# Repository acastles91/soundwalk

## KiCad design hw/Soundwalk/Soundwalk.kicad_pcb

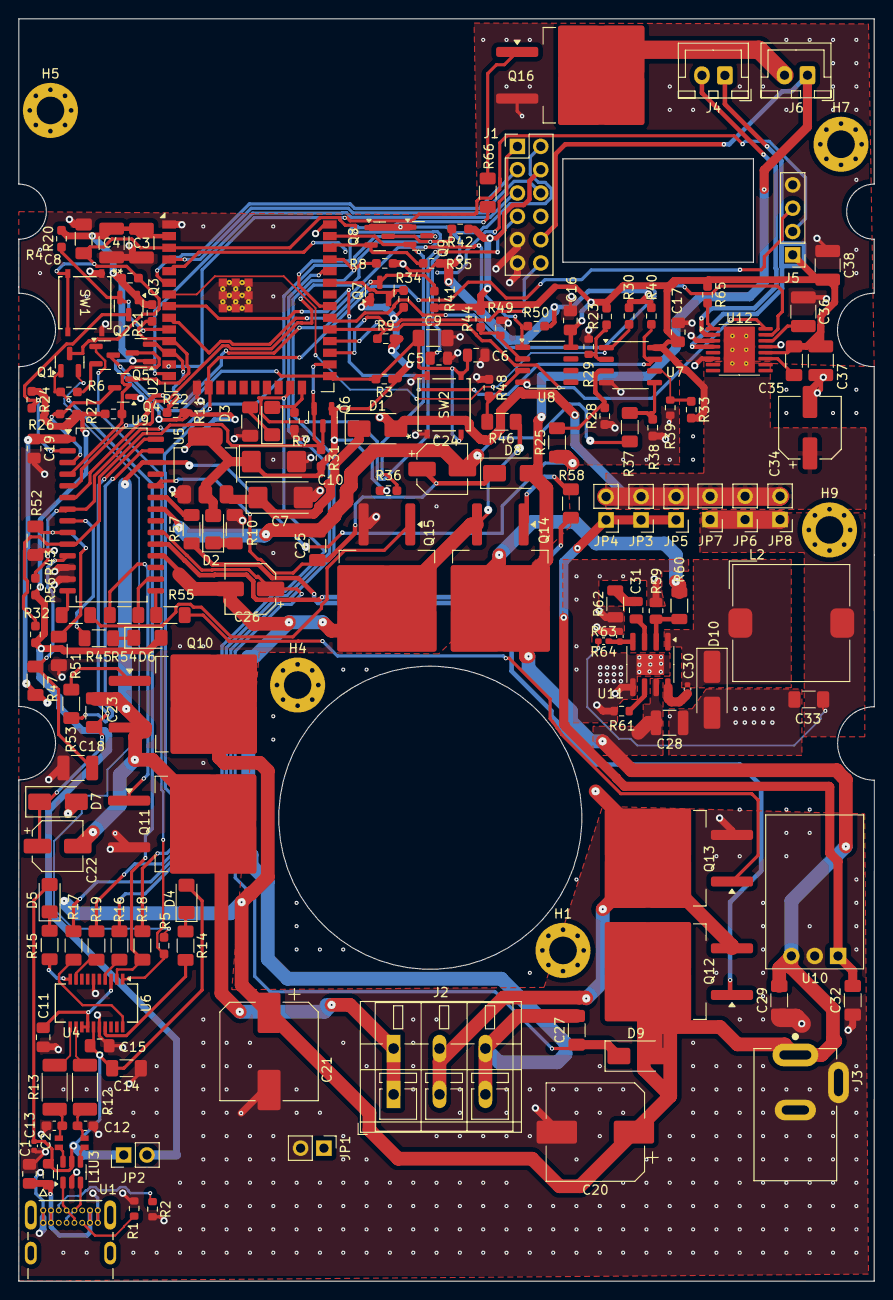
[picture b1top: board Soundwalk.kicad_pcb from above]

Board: 4 copper layers, 93.1 x 137.5 mm, 165 parts (0 on the bottom side), 109 nets.

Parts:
C1, C11, C15, C16, C17, C19: 0.1uF X7R 50V 0805; C_0805_2012Metric_Pad1.18x1.45mm_HandSolder
C2: 100n; C_0402_1005Metric
C3, C36, C37, C38: 10uF; C_1210_3225Metric_Pad1.33x2.70mm_HandSolder
C4: 22uF; C_1210_3225Metric_Pad1.33x2.70mm_HandSolder
C5, C6: 1uF; C_0805_2012Metric
C7, C10: 10uF 25V 2312 Tantalum; CP_EIA-6032-15_Kemet-U
C8, C9, C35: 0.1uF; C_1206_3216Metric_Pad1.33x1.80mm_HandSolder
C12, C13: 47pF; C_0603_1608Metric_Pad1.08x0.95mm_HandSolder
C14: 4.7uF 16V 1206 Tantalum; C_1206_3216Metric_Pad1.33x1.80mm_HandSolder
C18: 10uF 50V X7R; C_1210_3225Metric_Pad1.33x2.70mm_HandSolder
C20, C21: 330uF 35V; CP_Elec_10x10.5
C22, C24, C26: 10uF; CP_Elec_5x5.7
C23, C25, C27: 10uF 50V X7R; C_1206_3216Metric_Pad1.33x1.80mm_HandSolder
C28: 10uF 50V X7R 1210; C_1210_3225Metric
C29, C32, C33: 22uF 6.3V; C_1206_3216Metric_Pad1.33x1.80mm_HandSolder
C30: 100nF; C_0402_1005Metric
C31: 150pF 0805; C_0805_2012Metric
C34: C_Polarized; CP_Elec_6.3x5.9
D1: SS14; D_SMA
D2, D4, D5: LED - Yellow; LED_1206_3216Metric_Pad1.42x1.75mm_HandSolder
D3, D6: LED - Red; LED_1206_3216Metric_Pad1.42x1.75mm_HandSolder
D7, D8, D9: US1J; D_SMA
D10: D_Schottky; D_SMA_Handsoldering
H1, H4, H5, H7, H9: MountingHole_Pad; MountingHole_3mm_Pad_Via
J1: Conn_02x06_Odd_Even; PinHeader_2x06_P2.54mm_Vertical
J2: Screw_Terminal_01x03; TerminalBlock_WAGO_236-403_1x03_P5.00mm_45Degree
J3: PJ-002B; CUI_PJ-002B
J4, J6: Screw_Terminal_01x02; JST_XH_B2B-XH-A_1x02_P2.50mm_Vertical
J5: Conn_01x04_Socket; PinHeader_1x04_P2.54mm_Vertical
JP1, JP2, JP3, JP4, JP5, JP6, JP7, JP8: Jumper_2_Open; PinHeader_1x02_P2.54mm_Vertical
L1: L_Ferrite; L_0805_2012Metric_Pad1.05x1.20mm_HandSolder
L2: 15uH; L_TDK_SLF12565
Q1, Q2: S8050; SOT-23
Q3, Q4, Q5, Q6, Q7, Q8, Q9: 2N7002E; SOT-23
Q10, Q11, Q12, Q13, Q14, Q15, Q16: IRLZ44N; TO-263-2
R1, R2, R29, R39, R49: 5.1k; R_0603_1608Metric
R3, R4, R5, R6, R7, R8, R9, R20, R21, R22, R23, R24, R26, R27, R28, R30, R31, R32, R33, R34, R35, R36, R38, R40, R41, R42, R43, R44, R48, R50, R65: 10K; R_0603_1608Metric_Pad0.98x0.95mm_HandSolder
R10, R11: 220R; R_1206_3216Metric_Pad1.30x1.75mm_HandSolder
R12, R13: 27R; R_2010_5025Metric_Pad1.40x2.65mm_HandSolder
R14, R15, R16, R17, R45, R51, R53, R57, R58, R66: 1K; R_1206_3216Metric_Pad1.30x1.75mm_HandSolder
R18, R19: 0R; R_1206_3216Metric_Pad1.30x1.75mm_HandSolder
R25, R37, R46: 33K; R_1206_3216Metric_Pad1.30x1.75mm_HandSolder
R47: 100K; R_1206_3216Metric_Pad1.30x1.75mm_HandSolder
R52: 1M; R_1206_3216Metric_Pad1.30x1.75mm_HandSolder
R54, R55, R56: 100R; R_1206_3216Metric_Pad1.30x1.75mm_HandSolder
R59: 17.4K 0805; R_0805_2012Metric
R60, R62: 100K 1206; R_1206_3216Metric
R61: 200K 0603; R_0603_1608Metric
R63: 40.2k; C_0402_1005Metric_Pad0.74x0.62mm_HandSolder
R64: 210k; C_0402_1005Metric_Pad0.74x0.62mm_HandSolder
SW1, SW2: PTS526 SM15 SMTR2 LFS; SON4_PTS526 SM15 SMTR2 LFS_CNK
U1: 2137160001-Molex-USB-C-Connector; MOLEX_2137160001
U2: ESP32-WROOM-E; ESP32-WROOM-32E
U3: USBLC6-2SC6; SOT-23-6
U4: SRF3216A-Common_Mode_Choke; Bourns_SRF3216A
U5: NCP1117-3.3_SOT223; SOT-223-3_TabPin2
U6: FT231XS; SSOP-20_3.9x8.7mm_P0.635mm
U7, U8: LM393; SOP-8_3.9x4.9mm_P1.27mm
U9: IR2136; SOIC-28W_7.5x18.7mm_P1.27mm
U10: OKI-78SR-5_1.5-W36H-C; Converter_DCDC_Murata_OKI-78SR_Horizontal
U11: SOIC-8-1EP_3.9x4.9mm_P1.27mm_EP2.29x3mm
U12: DRV8833PWP; HTSSOP-16-1EP_4.4x5mm_P0.65mm_EP3.4x5mm_Mask2.46x2.31mm_The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

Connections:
+3.3V: C3.1, C4.1, C10.1, D2.2 (A), J1.2, Q3.1 (G), Q4.1 (G), Q5.1 (G), Q6.1 (G), Q7.1 (G), Q8.1 (G), Q9.1 (G), R3.1, R4.1, R8.2, R9.2, R20.2, R21.2, R22.2, R30.1, R31.2, R34.2, R35.2, R36.2, R40.1, R50.1, U2.2 (3V3), U5.2 (VO)
+5V: C16.1, C17.1, C34.1, C35.2, C37.2, C38.1, D1.2 (A), D6.2 (A), J1.4, J5.1, JP2.2 (B), JP3.2 (B), JP4.2 (B), JP5.2 (B), JP6.2 (B), JP7.2 (B), JP8.2 (B), R23.2, R24.1, R26.1, R27.1, R32.1, R33.2, R41.1, R42.1, R43.1, R44.2, R65.1, U7.8 (V+), U8.8 (V+), U12.12 (VM)
+12V: C19.1, C20.1, C21.1, C28.2, C29.2, D7.2 (A), D8.2 (A), D9.2 (A), J1.10, J3.1, J6.1, Q10.2 (D), Q12.2 (D), Q14.2 (D), R47.2, R60.2, U9.1 (VCC), U10.1 (IN), U11.7 (VIN)
/3-PH/3PH-ZC1: R30.2, U2.7 (GPIO35/ADC1_CH7), U7.1
/3-PH/3PH-ZC2: R40.2, U2.8 (32K_XP/GPIO32/ADC1_CH4), U7.7
/3-PH/3PH-ZC3: R50.2, U2.9 (32K_XN/GPIO33/ADC1_CH5), U8.1
/3-PH/HIN1: Q3.3 (D), R24.2, U9.2 (HIN1)
/3-PH/HIN2: Q4.3 (D), R26.2, U9.3 (HIN2)
/3-PH/HIN3: Q5.3 (D), R27.2, U9.4 (HIN3)
/3-PH/IR2136-EN: Q6.2 (S), Q6.3 (D), R31.1, R32.2, U2.26 (ADC2_CH0/GPIO4), U9.10 (EN)
/3-PH/IR2136-FAULT: R45.2, U9.8 (FAULT)
/3-PH/IR2136-FAULT-LED: D6.1 (K), R45.1
/3-PH/IR2136-HO1: R53.2, U9.27 (HO1)
/3-PH/IR2136-HO1-R: Q10.1 (G), R53.1
/3-PH/IR2136-HO2: R57.2, U9.23 (HO2)
/3-PH/IR2136-HO2-R: Q12.1 (G), R57.1
/3-PH/IR2136-HO3: R58.2, U9.19 (HO3)
/3-PH/IR2136-HO3-R: Q14.1 (G), R58.1
/3-PH/IR2136-ITRIP: R51.1, R52.2, U9.9 (ITRIP)
/3-PH/IR2136-LIN1: Q7.2 (S), R34.1, U2.33 (GPIO21)
/3-PH/IR2136-LIN2: Q8.2 (S), R35.1, U2.36 (GPIO22)
/3-PH/IR2136-LIN3: Q9.2 (S), R36.1, U2.37 (GPIO23)
/3-PH/IR2136-LO1: R54.2, U9.16 (LO1)
/3-PH/IR2136-LO1-R: Q11.1 (G), R54.1
/3-PH/IR2136-LO2: R55.2, U9.15 (LO2)
/3-PH/IR2136-LO2-R: Q13.1 (G), R55.1
/3-PH/IR2136-LO3: R56.2, U9.14 (LO3)
/3-PH/IR2136-LO3-R: Q15.1 (G), R56.1
/3-PH/IR2136-RCIN: C18.1, R47.1, U9.11 (RCIN)
/3-PH/IR2136-VB1: C22.1, C23.1, D7.1 (K), U9.28 (VB1)
/3-PH/IR2136-VB2: C24.1, C25.1, D8.1 (K), U9.24 (VB2)
/3-PH/IR2136-VB3: C26.1, C27.1, D9.1 (K), U9.20 (VB3)
/3-PH/IR2136_HIN1: Q3.2 (S), R20.1, U2.10 (DAC_1/ADC2_CH8/GPIO25)
/3-PH/IR2136_HIN2: Q4.2 (S), R21.1, U2.11 (DAC_2/ADC2_CH9/GPIO26)
/3-PH/IR2136_HIN3: Q5.2 (S), R22.1, U2.12 (ADC2_CH7/GPIO27)
/3-PH/IR2136_VS1: C22.2, C23.2, J2.1, Q10.3 (S), Q11.2 (D), R25.1, U9.26 (VS1)
/3-PH/IR2136_VS2: C24.2, C25.2, J2.2, Q12.3 (S), Q13.2 (D), R37.1, U9.22 (VS2)
/3-PH/IR2136_VS3: C26.2, C27.2, J2.3, Q14.3 (S), Q15.2 (D), R46.1, U9.18 (VS3)
/3-PH/LIN1: Q7.3 (D), R41.2, U9.5 (LIN1)
/3-PH/LIN2: Q8.3 (D), R42.2, U9.6 (LIN2)
/3-PH/LIN3: Q9.3 (D), R43.2, U9.7 (LIN3)
/3-PH/LM393-COIL1: R25.2, R28.2, U7.3 (+)
/3-PH/LM393-COIL2: R37.2, R38.2, U7.5 (+)
/3-PH/LM393-COIL3: R46.2, R48.2, U8.3 (+)
/3-PH/LM393-VREF1: R23.1, R29.1, U7.2 (-)
/3-PH/LM393-VREF2: R33.1, R39.1, U7.6 (-)
/3-PH/LM393-VREF3: R44.1, R49.1, U8.2 (-)
/ESP32-WROOM-32/ESP32-12VLED: R66.2, U2.31 (GPIO19)
/ESP32-WROOM-32/ESP32-AIN2: U2.30 (GPIO18), U12.15 (AIN2)
/ESP32-WROOM-32/ESP32-AUX-1: J1.8, U2.28 (GPIO17)
/ESP32-WROOM-32/ESP32-AUX-2: J1.12, U2.27 (GPIO16)
/ESP32-WROOM-32/ESP32-AUX-4: J1.5, U2.14 (MTDI/GPIO12/ADC2_CH5)
/ESP32-WROOM-32/ESP32-AUX-5: J1.7, R19.1, U2.23 (MTDO/GPIO15/ADC2_CH3)
/ESP32-WROOM-32/ESP32-AUX-6: J1.3, U2.6 (GPIO34/ADC1_CH6)
/ESP32-WROOM-32/ESP32-ENABLE: C5.1, C8.1, Q1.3 (C), R4.2, SW1.3, SW1.4, U2.3 (EN/CHIP_PU)
/ESP32-WROOM-32/ESP32-GPIO0: C6.1, C9.1, Q2.3 (C), R3.2, SW2.3, SW2.4, U2.25 (GPIO0/BOOT/ADC2_CH1)
/ESP32-WROOM-32/ESP32-GPIO2: D3.2 (A), R7.2, U2.24 (ADC2_CH2/GPIO2)
/ESP32-WROOM-32/ESP32-GPIO5: R9.1, U2.29 (GPIO5), U12.16 (AIN1)
/ESP32-WROOM-32/ESP32-GPIO13: J5.3, R18.1, U2.16 (MTCK/GPIO13/ADC2_CH4)
/ESP32-WROOM-32/ESP32-LED-CLK: J5.2, U2.13 (MTMS/GPIO14/ADC2_CH6)
/ESP32-WROOM-32/ESP32-RXD0: R17.1, U2.34 (U0RXD/GPIO3)
/ESP32-WROOM-32/ESP32-SENSOR-VN: J1.1, U2.5 (SENSOR_VN/GPIO39/ADC1_CH3)
/ESP32-WROOM-32/ESP32-SENSOR-VP: J1.6, U2.4 (SENSOR_VP/GPIO36/ADC1_CH0)
/ESP32-WROOM-32/ESP32-TXD0: R8.1, R16.1, U2.35 (U0TXD/GPIO1)
/ESP32-WROOM-32/FT231XS-CTS: R19.2, U6.9 (~CTS)
/ESP32-WROOM-32/FT231XS-DTR: Q2.1 (E), R5.1, U6.1 (~DTR)
/ESP32-WROOM-32/FT231XS-RTS: Q1.1 (E), R6.1, R18.2, U6.2 (~RTS)
/ESP32-WROOM-32/FT231XS-RXD: R16.2, U6.4 (RXD)
/ESP32-WROOM-32/FT231XS-TXD: R17.2, U6.20 (TXD)
/ESP32-WROOM-32/USBDM: R12.2, U6.12 (USBDM)
/ESP32-WROOM-32/USBDP: R13.2, U6.11 (USBDP)
/ESP32-WROOM-32/USB_CMC_D+: U3.6 (I/O1), U4.3
/ESP32-WROOM-32/USB_CMC_D-: U3.4 (I/O2), U4.4
/ESP32-WROOM-32/USB_CONN_CC1: R2.1, U1.A5 (CC1)
/ESP32-WROOM-32/USB_CONN_CC2: R1.1, U1.B5 (CC2)
/ESP32-WROOM-32/USB_CONN_D+: U1.A6 (DP1), U1.B6 (DP2), U3.1 (I/O1)
/ESP32-WROOM-32/USB_CONN_D-: U1.A7 (DN1), U1.B7 (DN2), U3.3 (I/O2)
/ESP32-WROOM-32/USB_FT231XS_D+: C13.1, R13.1, U4.2
/ESP32-WROOM-32/USB_FT231XS_D-: C12.1, R12.1, U4.1
/Power/EN: R59.2, R60.1, U11.2 (EN)
GND: C1.2, C2.1, C3.2, C4.2, C5.2, C6.2, C7.2, C8.2, C9.2, C10.2, C11.2, C12.2, C13.2, C14.2, C15.2, C16.2, C17.2, C18.2, C19.2, C20.2, C21.2, C28.1, C29.1, C32.1, C33.1, C34.2, C36.1, C37.1, C38.2, D10.2 (A), J1.9, J1.11, J3.2, J3.3, J5.4, JP1.2 (B), Q11.3 (S), Q13.3 (S), Q15.3 (S), Q16.3 (S), R1.2, R2.2, R7.1, R10.1, R11.1, R28.1, R29.2, R38.1, R39.2, R48.1, R49.2, R51.2, R52.1, R59.1, R61.1, R62.1, R63.1, SW1.1, SW1.2, SW2.1, SW2.2, U1.A1 (GND), U1.A12 (GND), U1.B1 (GND), U1.B12 (GND), U2.1 (GND), U2.15 (GND), U2.38 (GND), U2.39 (GND_THERMAL), U3.2 (GND), U5.1 (GND), U6.6 (GND), U6.16 (GND), U7.4 (V-), U8.4 (V-), U9.12 (VSS), U9.13 (COM), U10.2 (GND), U11.5 (GND), U11.9 (PAD), U12.3 (AISEN), U12.6 (BISEN), U12.13 (GND), U12.17 (GND)
unnamed: C31.1, R62.2
unnamed: C7.1, D1.1 (K), U5.3 (VI)
unnamed: D2.1 (K), R10.2
unnamed: D3.1 (K), R11.2
unnamed: D4.1 (K), R14.1
unnamed: D5.1 (K), R15.1
unnamed: C30.2, D10.1 (K), L2.1, U11.1 (SW)
unnamed: J4.1, U12.4 (AOUT2)
unnamed: J4.2, U12.2 (AOUT1)
unnamed: J6.2, Q16.2 (D)
unnamed: H1.1, H4.1, H5.1, H7.1, H9.1, JP1.1 (A)
unnamed: C32.2, JP3.1 (A), JP4.1 (A), JP5.1 (A), U10.3 (OUT)
unnamed: C33.2, JP6.1 (A), JP7.1 (A), JP8.1 (A), L2.2, R64.2
unnamed: Q1.2 (B), R5.2
unnamed: Q2.2 (B), R6.2
unnamed: Q16.1 (G), R66.1
unnamed: C11.1, U6.3 (VCCIO), U6.13 (3V3OUT), U6.14 (~RESET)
unnamed: R14.2, U6.17 (CBUS1)
unnamed: R15.2, U6.10 (CBUS2)
unnamed: C30.1, U11.8 (BST)
unnamed: C31.2, U11.3 (COMP)
unnamed: R63.2, R64.1, U11.4 (FB)
unnamed: R61.2, U11.6 (RSET)
unnamed: C35.1, U12.11 (VCP)
unnamed: C36.2, U12.14 (VINT)
unnamed: R65.2, U12.1 (~SLEEP)
V-BUS: C1.1, L1.1, U1.A4 (V-BUS), U1.A9 (V-BUS), U1.B4 (V-BUS), U1.B9 (V-BUS)
VBUS: C2.2, C14.1, C15.1, D4.2 (A), D5.2 (A), JP2.1 (A), L1.2, U3.5 (VBUS), U6.15 (VCC)

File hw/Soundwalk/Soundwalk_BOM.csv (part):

Reference,Value,Datasheet,Footprint,Qty,DNP,Digi+AC0-Key+AF8-PN,Digikey+AF8-PN,Digikey+AF8-Pn,MPN,Manufacturer+AF8-PN
+ACI-R18,R19+ACI-,0R,+AH4-,Resistor+AF8-SMD:R+AF8-1206+AF8-3216Metric+AF8-Pad1.30x1.75mm+AF8-HandSolder,2,,,,,RC0603FR+AC0-075K1L,
+ACI-C12,C13+ACI-,47pF,+AH4-,Capacitor+AF8-SMD:C+AF8-0603+AF8-1608Metric+AF8-Pad1.08x0.95mm+AF8-HandSolder,2,,,712+AC0-QSCP251Q470J1GV001TTR+AC0-ND,,QSCP251Q470J1GV001T,
+ACI-C8,C9,C35+ACI-,0.1uF,+AH4-,Capacitor+AF8-SMD:C+AF8-1206+AF8-3216Metric+AF8-Pad1.33x1.80mm+AF8-HandSolder,3,,,,,,
C2,100n,https://search.murata.co.jp/Ceramy/image/img/A01X/G101/ENG/G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,Capacitor+AF8-SMD:C+AF8-0402+AF8-1005Metric,1,,,,,EMK105B7104KV+AC0-F,
C30,100nF,+AH4-,Capacitor+AF8-SMD:C+AF8-0402+AF8-1005Metric,1,,,1276+AC0-CL05B104KP5VPNCTR+AC0-ND,,CL05B104KP5VPNC,
+ACI-C5,C6+ACI-,1uF,+AH4-,Capacitor+AF8-SMD:C+AF8-0805+AF8-2012Metric,2,,,,,,
+ACI-C3,C36,C37,C38+ACI-,10uF,+AH4-,Capacitor+AF8-SMD:C+AF8-1210+AF8-3225Metric+AF8-Pad1.33x2.70mm+AF8-HandSolder,4,,,,,,
+ACI-C22,C24,C26+ACUAJAAl-x+ACI-,10uF,+AH4-,Capacitor+AF8-SMD:CP+AF8-Elec+AF8-5x5.7,3,DNP,,,,,
L2,15uH,+AH4-,Inductor+AF8-SMD:L+AF8-TDK+AF8-SLF12565,1,,,445+AC0-3842+AC0-2+AC0-ND,,SLF12565T+AC0-150M4R2+AC0-H,
C4,22uF,+AH4-,Capacitor+AF8-SMD:C+AF8-1210+AF8-3225Metric+AF8-Pad1.33x2.70mm+AF8-HandSolder,1,,,,,,
+ACI-R12,R13+ACI-,27R,+AH4-,Resistor+AF8-SMD:R+AF8-2010+AF8-5025Metric+AF8-Pad1.40x2.65mm+AF8-HandSolder,2,,,,,CRGP2010F27R,
+ACI-R54,R55,R56+ACI-,100R,+AH4-,Resistor+AF8-SMD:R+AF8-1206+AF8-3216Metric+AF8-Pad1.30x1.75mm+AF8-HandSolder,3,,,,,,
+ACI-R10,R11+ACI-,220R,+AH4-,Resistor+AF8-SMD:R+AF8-1206+AF8-3216Metric+AF8-Pad1.30x1.75mm+AF8-HandSolder,2,,,,,,
+ACI-R14,R15,R16,R17,R45,R51,R53,R57,R58,R66+ACI-,1K,+AH4-,Resistor+AF8-SMD:R+AF8-1206+AF8-3216Metric+AF8-Pad1.30x1.75mm+AF8-HandSolder,10,,,,,+AC0ALQ- mixed values +AC0ALQ-,
+ACI-R1,R2,R29,R39,R49+ACI-,5.1k,+AH4-,Resistor+AF8-SMD:R+AF8-0603+AF8-1608Metric,5,,,,,RC0603FR+AC0-075K1L,
+ACI-R3,R4,R5,R6,R7,R8,R9,R20,R21,R22,R23,R24,R26,R27,R28,R30,R31,R32,R33,R34,R35,R36,R38,R40,R41,R42,R43,R44,R48,R50,R65+ACI-,10K,+AH4-,Resistor+AF8-SMD:R+AF8-0603+AF8-1608Metric+AF8-Pad0.98x0.95mm+AF8-HandSolder,31,,,,,,
+ACI-R25,R37,R46+ACI-,33K,+AH4-,Resistor+AF8-SMD:R+AF8-1206+AF8-3216Metric+AF8-Pad1.30x1.75mm+AF8-HandSolder,3,,,RMCF1206FT33K2TR+AC0-ND,,RMCF1206FT33K2,
R63,40.2k,+AH4-,Capacitor+AF8-SMD:C+AF8-0402+AF8-1005Metric+AF8-Pad0.74x0.62mm+AF8-HandSolder,1,,,P40.2KLTR+AC0-ND,,ERJ+AC0-2RKF4022X,
R47,100K,+AH4-,Resistor+AF8-SMD:R+AF8-1206+AF8-3216Metric+AF8-Pad1.30x1.75mm+AF8-HandSolder,1,,,,,,
R64,210k,+AH4-,Capacitor+AF8-SMD:C+AF8-0402+AF8-1005Metric+AF8-Pad0.74x0.62mm+AF8-HandSolder,1,,,2019+AC0-RK73H1ETTP2103FTR+AC0-ND,,RK73H1ETTP2103F,
R52,1M,+AH4-,Resistor+AF8-SMD:R+AF8-1206+AF8-3216Metric+AF8-Pad1.30x1.75mm+AF8-HandSolder,1,,,,,,
U1,2137160001+AC0-Molex+AC0-USB+AC0-C+AC0-Connector,https://www.molex.com/en+AC0-us/products/part+AC0-detail+AC0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,privateParts:MOLEX+AF8-2137160001,1,,,,,,
+ACI-C1,C11,C15,C16,C17,C19+ACI-,0.1uF X7R 50V 0805,+AH4-,Capacitor+AF8-SMD:C+AF8-0805+AF8-2012Metric+AF8-Pad1.18x1.45mm+AF8-HandSolder,6,,,,,,
+ACI-R60,R62+ACI-,100K 1206,+AH4-,Resistor+AF8-SMD:R+AF8-1206+AF8-3216Metric,2,,,,,,
+ACI-C7,C10+ACI-,10uF 25V 2312 Tantalum,+AH4-,Capacitor+AF8-Tantalum+AF8-SMD:CP+AF8-EIA+AC0-6032+AC0-15+AF8-Kemet+AC0-U,2,,,399+AC0-10160+AC0-2+AC0-ND,,T491C106M025AT7280,
+ACI-C18,C23,C25,C27+ACI-,10uF 50V X7R,+AH4-,+AC0ALQ- mixed values +AC0ALQ-,4,,+AC0ALQ- mixed values +AC0ALQ-,,,,+AC0ALQ- mixed values +AC0ALQ-
C28,10uF 50V X7R 1210,+AH4-,Capacitor+AF8-SMD:C+AF8-1210+AF8-3225Metric,1,,,1276+AC0-3388+AC0-2+AC0-ND,,CL32B106KBJNNWE,
C31,150pF 0805,+AH4-,Capacitor+AF8-SMD:C+AF8-0805+AF8-2012Metric,1,,,399+AC0-C0402C151K5RACTUTR+AC0-ND,,C0402C151K5RACTU,
R59,17.4K 0805,+AH4-,Resistor+AF8-SMD:R+AF8-0805+AF8-2012Metric,1,,,RMCF0805FT17K4TR+AC0-ND,,RMCF0805FT17K4,
R61,200K 0603,+AH4-,Resistor+AF8-SMD:R+AF8-0603+AF8-1608Metric,1,,,311+AC0-200KGRTR+AC0-ND,,RC0603JR+AC0-07200KL,
+ACI-C29,C32,C33+ACI-,22uF 6.3V,+AH4-,Capacitor+AF8-SMD:C+AF8-1206+AF8-3216Metric+AF8-Pad1.33x1.80mm+AF8-HandSolder,3,,,478+AC0-12066C226MAT2A+AFw-2.5KTR+AC0-ND,,12066C226MAT2A+AFw-2.5K,
+ACI-Q3,Q4,Q5,Q6,Q7,Q8,Q9+ACI-,2N7002E,http://www.diodes.com/assets/Datasheets/ds30376.pdf,Package+AF8-TO+AF8-SOT+AF8-SMD:SOT+AC0-23,7,,,,,,
C20,330uF 35V,,Capacitor+AF8-SMD:CP+AF8-Elec+AF8-10x10.5,1,DNP,565+AC0-4786+AC0-1+AC0-ND,,,,HHXC500ARA101MJA0G
C21,330uF 35V,,Capacitor+AF8-SMD:CP+AF8-Elec+AF8-10x10.5,1,,565+AC0-4786+AC0-1+AC0-ND,,,,HHXC500ARA101MJA0G
C14,4.7uF 16V 1206 Tantalum,+AH4-,Capacitor+AF8-SMD:C+AF8-1206+AF8-3216Metric+AF8-Pad1.33x1.80mm+AF8-HandSolder,1,,,478+AC0-3868+AC0-2+AC0-ND,,TAJA475K016RNJ,
C34,C+AF8-Polarized,+AH4-,Capacitor+AF8-SMD:CP+AF8-Elec+AF8-6.3x5.9,1,,,399+AC0-A768EB107M1ELAS036TR+AC0-ND,,A768EB107M1ELAS036,
J5,Conn+AF8-01x04+AF8-Socket,+AH4-,Connector+AF8-PinHeader+AF8-2.54mm:PinHeader+AF8-1x04+AF8-P2.54mm+AF8-Vertical,1,,,,,,
J1,Conn+AF8-02x06+AF8-Odd+AF8-Even,+AH4-,Connector+AF8-PinHeader+AF8-2.54mm:PinHeader+AF8-2x06+AF8-P2.54mm+AF8-Vertical,1,,,,,,
D10,D+AF8-Schottky,+AH4-,Diode+AF8-SMD:D+AF8-SMA+AF8-Handsoldering,1,,,B340A+AC0-FDITR+AC0-ND,,B340A+AC0-13+AC0-F,
U12,DRV8833PWP,http://www.ti.com/lit/ds/symlink/drv8833.pdf,Package+AF8-SO:HTSSOP+AC0-16+AC0-1EP+AF8-4.4x5mm+AF8-P0.65mm+AF8-EP3.4x5mm+AF8-Mask2.46x2.31mm+AF8-ThermalVias,1,,,,,,
U2,ESP32+AC0-WROOM+AC0-E,https://www.espressif.com/sites/default/files/documentation/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,RF+AF8-Module:ESP32+AC0-WROOM+AC0-32E,1,,,,,,
U6,FT231XS,https://www.ftdichip.com/Support/Documents/DataSheets/ICs/DS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,Package+AF8-SO:SSOP+AC0-20+AF8-3.9x8.7mm+AF8-P0.635mm,1,,,768+AC0-1156+AC0-5+AC0-ND,,FT231XS+AC0-U,
U9,IR2136,,Package+AF8-SO:SOIC+AC0-28W+AF8-7.5x18.7mm+AF8-P1.27mm,1,,IR2136SPBF+AC0-ND,,,,IR2136SPBF
+ACI-Q10,Q11,Q12,Q13,Q14,Q15,Q16+ACI-,IRLZ44N,http://www.irf.com/product+AC0-info/datasheets/data/irlz44n.pdf,Package+AF8-TO+AF8-SOT+AF8-SMD:TO+AC0-263+AC0-2,7,,,IRLZ44NSTRLPBFTR+AC0-ND,,IRLZ44NSTRLPBF,
+ACI-JP1,JP2,JP3,JP4,JP5,JP6,JP7,JP8+ACI-,Jumper+AF8-2+AF8-Open,+AH4-,Connector+AF8-PinHeader+AF8-2.54mm:PinHeader+AF8-1x02+AF8-P2.54mm+AF8-Vertical,8,,,,,,
L1,L+AF8-Ferrite,+AH4-,Inductor+AF8-SMD:L+AF8-0805+AF8-2012Metric+AF8-Pad1.05x1.20mm+AF8-HandSolder,1,,,240+AC0-2399+AC0-2+AC0-ND,,HZ0805E601R+AC0-10,
+ACI-D3,D6+ACI-,LED +AC0- Red,+AH4-,LED+AF8-SMD:LED+AF8-1206+AF8-3216Metric+AF8-Pad1.42x1.75mm+AF8-HandSolder,2,,,754+AC0-1143+AC0-2+AC0-ND,,APT3216SURCK,
+ACI-D2,D4,D5+ACI-,LED +AC0- Yellow,+AH4-,LED+AF8-SMD:LED+AF8-1206+AF8-3216Metric+AF8-Pad1.42x1.75mm+AF8-HandSolder,3,,,,,,
+ACI-U7,U8+ACI-,LM393,http://www.ti.com/lit/ds/symlink/lm393.pdf,Package+AF8-SO:SOP+AC0-8+AF8-3.9x4.9mm+AF8-P1.27mm,2,,,,497+AC0-18379+AC0-ND,LM393D,
U5,NCP1117+AC0-3.3+AF8-SOT223,http://www.onsemi.com/pub+AF8-link/Collateral/NCP1117+AC0-D.PDF,Package+AF8-TO+AF8-SOT+AF8-SMD:SOT+AC0-223+AC0-3+AF8-TabPin2,1,,,NCP1117LPST33T3GOSTR+AC0-ND,,NCP1117LPST33T3G,
U10,OKI+AC0-78SR+AC0-5+AF8-1.5+AC0-W36H+AC0-C,https://power.murata.com/data/power/oki+AC0-78sr.pdf,Converter+AF8-DCDC:Converter+AF8-DCDC+AF8-Murata+AF8-OKI+AC0-78SR+AF8-Horizontal,1,,,,,,
J3,PJ+AC0-002B,,privateParts:CUI+AF8-PJ+AC0-002B,1,,,CP+AC0-002B+AC0-ND,, PJ+AC0-002B,
+ACI-SW1,SW2+ACI-,PTS526 SM15 SMTR2 LFS,PTS526 SM15 SMTR2 LFS,SON4+AF8-PTS526 SM15 SMTR2 LFS+AF8-CNK,2,,,CKN12220+AC0-2+AC0-ND,,PTS526SM15SMTR2 LFS,
+ACI-Q1,Q2+ACI-,S8050,https://www.mccsemi.com/pdf/Products/MMSS8050(SOT+AC0-23).pdf,Package+AF8-TO+AF8-SOT+AF8-SMD:SOT+AC0-23,2,,,MMSS8050+AC0-H+AC0-TPMSCT+AC0-ND,,MMSS8050+AC0-H+AC0-TP,
+ACI-J4,J6+ACI-,Screw+AF8-Terminal+AF8-01x02,+AH4-,Connector+AF8-JST:JST+AF8-XH+AF8-B2B+AC0-XH+AC0-A+AF8-1x02+AF8-P2.50mm+AF8-Vertical,2,,,,,,
J2,Screw+AF8-Terminal+AF8-01x03,+AH4-,TerminalBlock+AF8-WAGO:TerminalBlock+AF8-WAGO+AF8-236+AC0-403+AF8-1x03+AF8-P5.00mm+AF8-45Degree,1,,,,,,
U4,SRF3216A+AC0-Common+AF8-Mode+AF8-Choke,,privateParts:Bourns+AF8-SRF3216A,1,,SRF3216A+AC0-222YCT+AC0-ND,,,SRF3216A+AC0-222Y,
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
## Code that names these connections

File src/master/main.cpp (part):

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  {0,1,0},{0,0,1},{0,0,1},{1,0,0},{1,0,0},{0,1,0}
};
static inline void setHIN(uint8_t phase, bool on) {
  uint8_t pin = (phase==0)?HIN1:(phase==1)?HIN2:HIN3;
  pinMode(pin, OUTPUT);
  digitalWrite(pin, on ? HIGH : LOW);
}
static inline void setLIN(uint8_t phase, bool on) {
  uint8_t pin = (phase==0)?LIN1:(phase==1)?LIN2:LIN3;
  pinMode(pin, OUTPUT);
  digitalWrite(pin, on ? HIGH : LOW);
}
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  }
}
static void motorBringUpOnce() {
  pinMode(HIN1, OUTPUT); pinMode(HIN2, OUTPUT); pinMode(HIN3, OUTPUT);
  pinMode(LIN1, OUTPUT); pinMode(LIN2, OUTPUT); pinMode(LIN3, OUTPUT);
  pinMode(ENABLE, OUTPUT); digitalWrite(ENABLE, HIGH);
  alignHold(0, 800);
  commutateSweep(/*delay_ms*/ 30, /*cycles*/ 20);
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
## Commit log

2025-08-02 working, problems with back emf
2025-08-10 basic operation with 2 slaves
2025-08-17 it's getting there
2025-08-17 last chatgpt input
2025-08-19 at the recording studio
